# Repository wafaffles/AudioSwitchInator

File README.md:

# Audioswitchinator
A multi input and output audio switch with an integrated, toggleable Hifi phono preamp

## Shortcuts
- [Features](#features)
- [What is it?](#what-is-it)
- [Resources](#resources)
- [Assembly](#assembly)
- [Bill Of Materials](#bill-of-materials)
- [Photos](#photos)

## Audioswitchinator Zine

## Features
- 4 Inputs
  - 3 RCA
  - 1 3.5mm
- 2 Outputs
  - 2 RCA
- Audio Input and Output Selection
- Integrated Toggleable Phono Preamp for a Turntable

## What is it?

The Audioswitchinator is a device that was made to allow me to route all of my audio inputs and outputs into one place on my desk so that I can easily change where my audio is coming from and going to without having to deal with changing the input on my speakers, changing the output on my computer, and my record player mainly. It features 4 inputs, 3 RCA and 1 3.5mm ports, and 2 ouputs, both being RCA ports. The first of the phono inputs is routed to a toggleable phono preamp, based on this design by [Elliott Sound Products](https://sound-au.com/project06.htm). The mixture of inputs and ports allows for easily compatibility with most audio products, as well as supporting smaller on the go inputs like a phone or other input device. While I only need 2 inputs and 2 outputs currently, the device features the extra inputs and outputs as my equipment arsenal expands or I want to test new products without fully removing the old ones.

The device features a power switch on the rear to power the integrated phono preamp, a switch on the front to enable routing of the turntable input through the phono preamp, a rotary switch to choose which input you would like to listen to, and a switch to choose between either of the two inputs.
It is powered using 12V via a 5.7mm barrell jack. It has a very low power draw of around 50mA at most so nearly any suitable 12V switching mode power supply should work well.

The case is fully 3d printed with use of a few M4 bolts and heatset inserts, but can easily be modified to thread directly into the plastic. The design resembles the design pattern of Schiit Audio products as I currently own a DAC and headphone amp and really like the design. The case is at largest 160x80, so it is easily printable on most 3D printers, being designed to print on my Bambu Labs A1 Mini.

## Resources

CAD Link: https://cad.onshape.com/documents/9e04128c642e582e05c8193e/w/29af00c33977f5103195c9e0/e/9dcbf64564f57b3e7e8e01ad?renderMode=0&uiState=6a12269c000845437493f06b

CAD Files: [HERE](/Models)

ECAD Files: [HERE](/Models/ECAD/)

Production Files: [HERE](/Resources/)

## Assembly

You will need:
- PCB from files
- Soldering Iron & Solder
- All components from [BOM](https://docs.google.com/spreadsheets/d/1tNDlkv8S-ZhfvEyZw77WZDcWJRZpA8B7S98ZAzSkEbk/edit?usp=sharing.)
- Matching screwdriver to screw set (allen key in provided kit)
- Small pair of tweasers

To start, you will need to have access to a 3D printer with a build volume of at least 160x80mm and about 100-120g of filament of your choice.

You then need to order all the parts and PCB and have proper resources to solder these components. Once you have these, solder all components on as specified in the schematic.

Once soldered together where listed in the schematic, then with the bottom part of the case, insert the 8 heatset inserts if you choose not to modify the design to use those. To insert heatset inserts, get the largest tip that fits inside the heatset insert and install it on your soldering iron. Now, place the insert where it goes and insert the tip into the center of the insert snd heat it while applying slight downward force until it is flush with the surface. A small pair of tweasers may be helpful to reorient it.

Once all the heatset inserts are installed, you should be able to screw in the PCB, then screw on the top, and it should be working there!

## Bill Of Materials

Bill of Materials: [HERE](https://docs.google.com/spreadsheets/d/1tNDlkv8S-ZhfvEyZw77WZDcWJRZpA8B7S98ZAzSkEbk/edit?usp=sharing)

## Photos

Audioswitchinator PCB Schematic

Audioswitchinator Case Front

Audioswitchinator Case Back

Audioswitchinator Case Inside

PCB All Layers

PCB F.Cu Layer

PCB In1.Cu Layer

PCB In2.Cu Layer

PCB B.Cu Layer

Fromt of PCB

Back of PCB

## Credits

This project uses:

- [KiCad](https://www.kicad.org/)
- [Figma](https://www.figma.com/)
- [Hack Club Fallout](https://fallout.hackclub.com/path)

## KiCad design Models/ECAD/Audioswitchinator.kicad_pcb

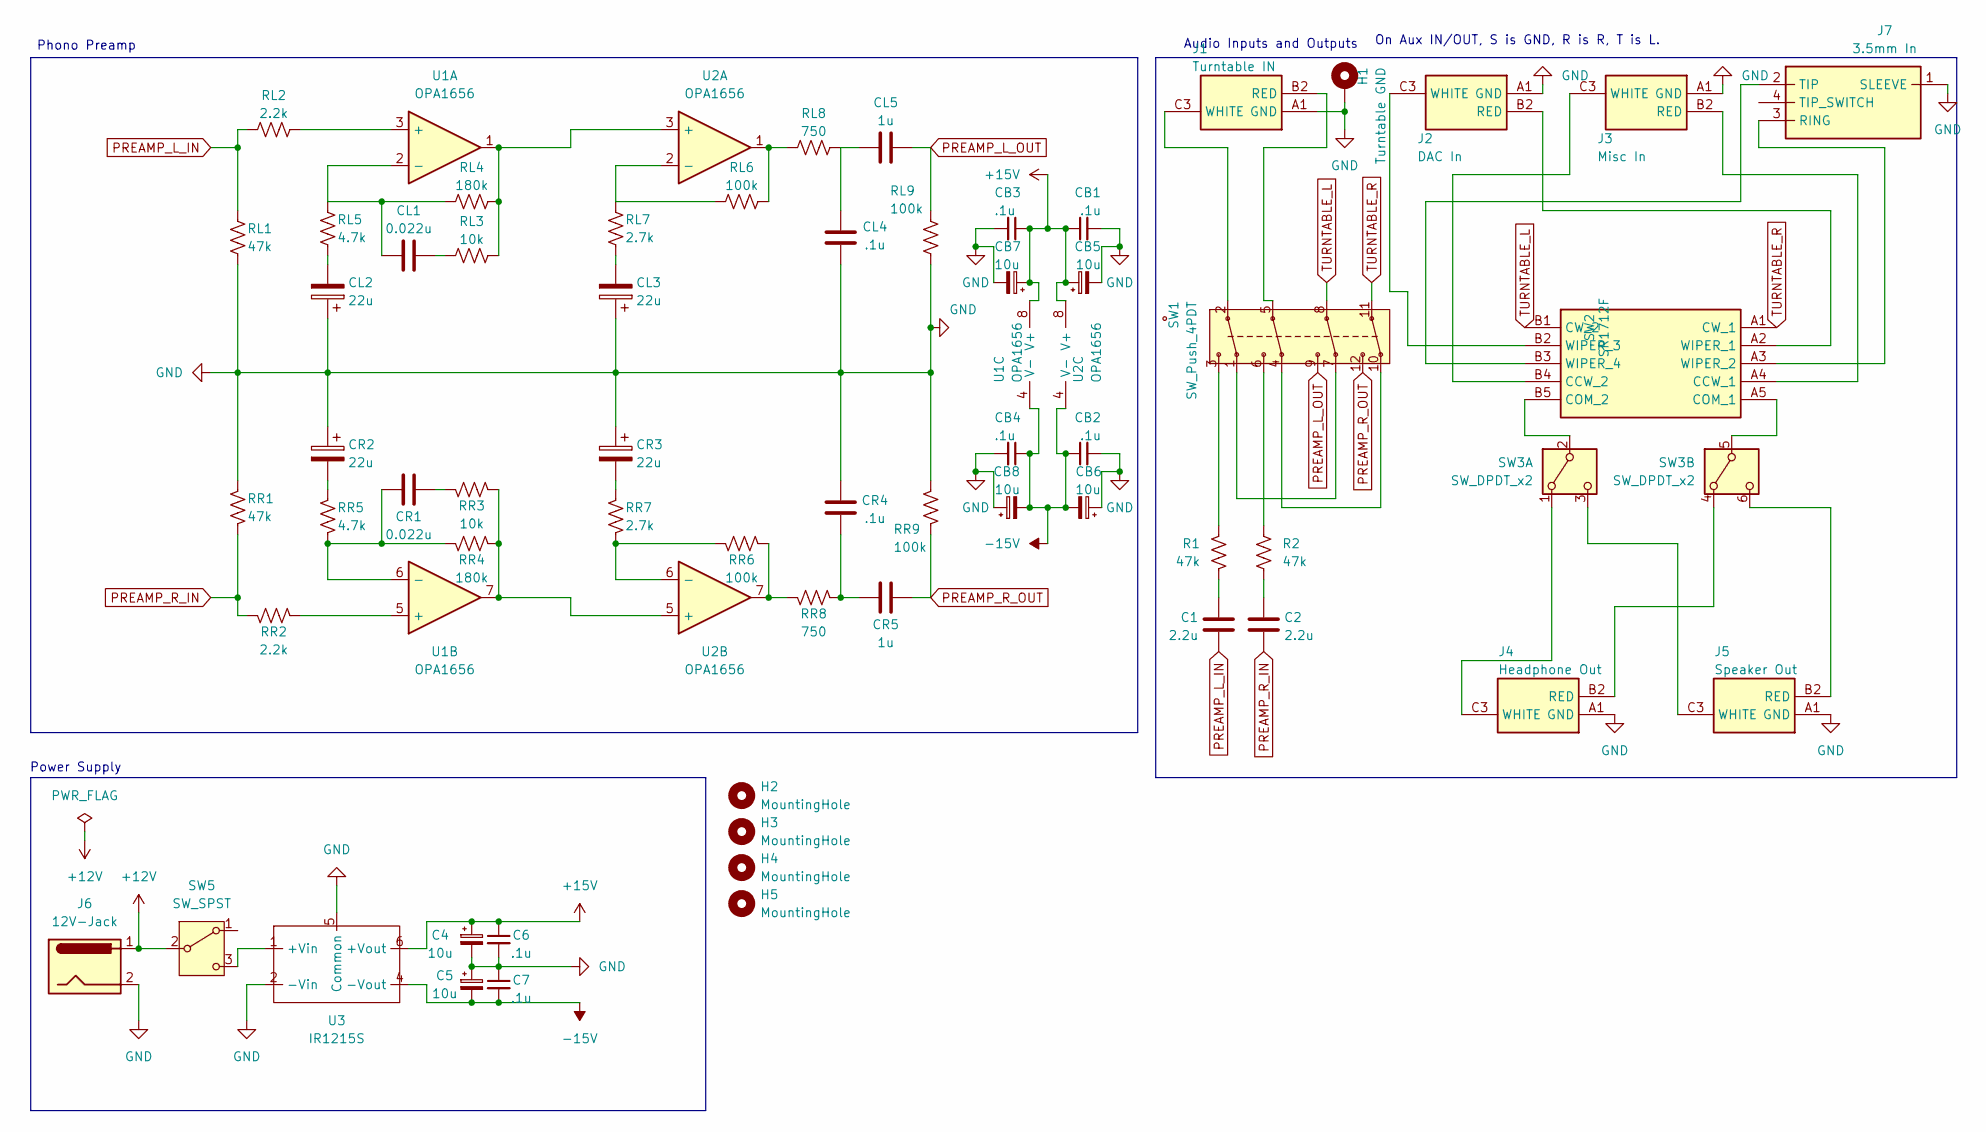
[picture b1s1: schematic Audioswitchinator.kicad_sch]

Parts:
C1, C2: 2.2u; C_Radial_D5.0mm_H11.0mm_P2.00mm
C4, C5: 10u; CP_Radial_D5.0mm_P2.00mm
C6, C7: .1u; C_Rect_L7.2mm_W2.5mm_P5.00mm
CB1, CB2, CB3, CB4: .1u; C_Rect_L7.2mm_W2.5mm_P5.00mm
CB5, CB6, CB7, CB8: 10u; CP_Radial_D5.0mm_P2.00mm
CL1: 0.022u; C_Rect_L13.0mm_W4.0mm_P10.00mm_FKS3_FKP3_MKS4
CL2, CL3: 22u; CP_Radial_D6.3mm_P2.50mm
CL4: .1u; C_Rect_L7.2mm_W2.5mm_P5.00mm
CL5: 1u; C_Radial_D5.0mm_H11.0mm_P2.00mm
CR1: 0.022u; C_Rect_L13.0mm_W4.0mm_P10.00mm_FKS3_FKP3_MKS4
CR2, CR3: 22u; CP_Radial_D6.3mm_P2.50mm
CR4: .1u; C_Rect_L7.2mm_W2.5mm_P5.00mm
CR5: 1u; C_Radial_D5.0mm_H11.0mm_P2.00mm
H1: Turntable GND; SolderWirePad_1x01_SMD_3x6mm
H2, H3, H4, H5: MountingHole; MountingHole_4.3mm_M4_Pad
J1: Turntable IN; 1564219E; Manufacturer_Part_Number 156-4219-E
J2: DAC In; 1564219E; Manufacturer_Part_Number 156-4219-E
J3: Misc In; 1564219E; Manufacturer_Part_Number 156-4219-E
J4: Headphone Out; 1564219E; Manufacturer_Part_Number 156-4219-E
J5: Speaker Out; 1564219E; Manufacturer_Part_Number 156-4219-E
J6: 12V-Jack; PJ059A
J7: 3.5mm In; SJ13554NG; Manufacturer_Part_Number SJ1-3554NG
R1, R2: 47k; R_1206_3216Metric_Pad1.30x1.75mm_HandSolder
RL1: 47k; R_1206_3216Metric_Pad1.30x1.75mm_HandSolder
RL2: 2.2k; R_1206_3216Metric_Pad1.30x1.75mm_HandSolder
RL3: 10k; R_1206_3216Metric_Pad1.30x1.75mm_HandSolder
RL4: 180k; R_1206_3216Metric_Pad1.30x1.75mm_HandSolder
RL5: 4.7k; R_1206_3216Metric_Pad1.30x1.75mm_HandSolder
RL6, RL9: 100k; R_1206_3216Metric_Pad1.30x1.75mm_HandSolder
RL7: 2.7k; R_1206_3216Metric_Pad1.30x1.75mm_HandSolder
RL8: 750; R_1206_3216Metric_Pad1.30x1.75mm_HandSolder
RR1: 47k; R_1206_3216Metric_Pad1.30x1.75mm_HandSolder
RR2: 2.2k; R_1206_3216Metric_Pad1.30x1.75mm_HandSolder
RR3: 10k; R_1206_3216Metric_Pad1.30x1.75mm_HandSolder
RR4: 180k; R_1206_3216Metric_Pad1.30x1.75mm_HandSolder
RR5: 4.7k; R_1206_3216Metric_Pad1.30x1.75mm_HandSolder
RR6, RR9: 100k; R_1206_3216Metric_Pad1.30x1.75mm_HandSolder
RR7: 2.7k; R_1206_3216Metric_Pad1.30x1.75mm_HandSolder
RR8: 750; R_1206_3216Metric_Pad1.30x1.75mm_HandSolder
SW1: SW_Push_4PDT; 1004P3T2B4M7QE
SW2: SR1712F; SRBM149501; Mouser Part Number 688-SRBM149501
SW3: SW_DPDT_x2; 100AWDP1T1B4M6QE
SW5: SW_SPST; ATE1D6M310Z
U1, U2: OPA1656; SOIC127P600X175-8N-OPA1656IDR
U3: IR1215S

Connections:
+12V: J6.1, SW5.2 (B)
+15V: C4.1, C6.1, CB1.1, CB3.1, CB5.1, CB7.1, U1.8 (V+), U2.8 (V+), U3.6 (+Vout)
-15V: C5.2, C7.2, CB2.1, CB4.1, CB6.2, CB8.2, U1.4 (V-), U2.4 (V-), U3.4 (-Vout)
GND: C4.2, C5.1, C6.2, C7.1, CB1.2, CB2.2, CB3.2, CB4.2, CB5.2, CB6.1, CB7.2, CB8.1, CL2.1, CL3.1, CL4.2, CR2.1, CR3.1, CR4.2, H1.1 (1_1), J1.A1 (GND), J2.A1 (GND), J3.A1 (GND), J4.A1 (GND), J5.A1 (GND), J6.2, J7.1 (SLEEVE), RL1.1, RL9.1, RR1.1, RR9.1, U3.2 (-Vin), U3.5 (Common)
unnamed: C1.1, R1.1
unnamed: C2.1, R2.1
unnamed: CL1.1, RL3.1
unnamed: CL2.2, RL5.1
unnamed: CL3.2, RL7.1
unnamed: CL4.1, CL5.2, RL8.2
unnamed: CR1.1, RR3.1
unnamed: CR2.2, RR5.1
unnamed: CR3.2, RR7.1
unnamed: CR4.1, CR5.2, RR8.2
unnamed: J1.B2 (RED), SW1.5
unnamed: J1.C3 (WHITE), SW1.2
unnamed: J2.B2 (RED), SW2.A2 (WIPER_1)
unnamed: J2.C3 (WHITE), SW2.B2 (WIPER_3)
unnamed: J3.B2 (RED), SW2.A4 (CCW_1)
unnamed: J3.C3 (WHITE), SW2.B4 (CCW_2)
unnamed: J4.B2 (RED), SW3.4 (A)
unnamed: J4.C3 (WHITE), SW3.1 (A)
unnamed: J5.B2 (RED), SW3.6 (C)
unnamed: J5.C3 (WHITE), SW3.3 (C)
unnamed: J7.3 (RING), SW2.A3 (WIPER_2)
unnamed: J7.2 (TIP), SW2.B3 (WIPER_4)
unnamed: R1.2, SW1.3
unnamed: R2.2, SW1.6
unnamed: RL6.2, RL8.1, U2.1
unnamed: RR6.2, RR8.1, U2.7
unnamed: SW1.1, SW1.7
unnamed: SW1.4, SW1.10
unnamed: SW2.A5 (COM_1), SW3.5 (B)
unnamed: SW2.B5 (COM_2), SW3.2 (B)
unnamed: SW5.3 (C), U3.1 (+Vin)
unnamed: RL2.2, U1.3 (+)
unnamed: CL1.2, RL4.1, RL5.2, U1.2 (-)
unnamed: RR2.2, U1.5 (+)
unnamed: CR1.2, RR4.1, RR5.2, U1.6 (-)
unnamed: RL3.2, RL4.2, U1.1, U2.3 (+)
unnamed: RL6.1, RL7.2, U2.2 (-)
unnamed: RR3.2, RR4.2, U1.7, U2.5 (+)
unnamed: RR6.1, RR7.2, U2.6 (-)
PREAMP_L_IN: C1.2, RL1.2, RL2.1
PREAMP_L_OUT: CL5.1, RL9.2, SW1.9
PREAMP_R_IN: C2.2, RR1.2, RR2.1
PREAMP_R_OUT: CR5.1, RR9.2, SW1.12
TURNTABLE_L: SW1.8, SW2.B1 (CW_2)
TURNTABLE_R: SW1.11, SW2.A1 (CW_1)

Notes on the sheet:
Power Supply
Audio Inputs and Outputs
On Aux IN/OUT, S is GND, R is R, T is L.
Phono Preamp

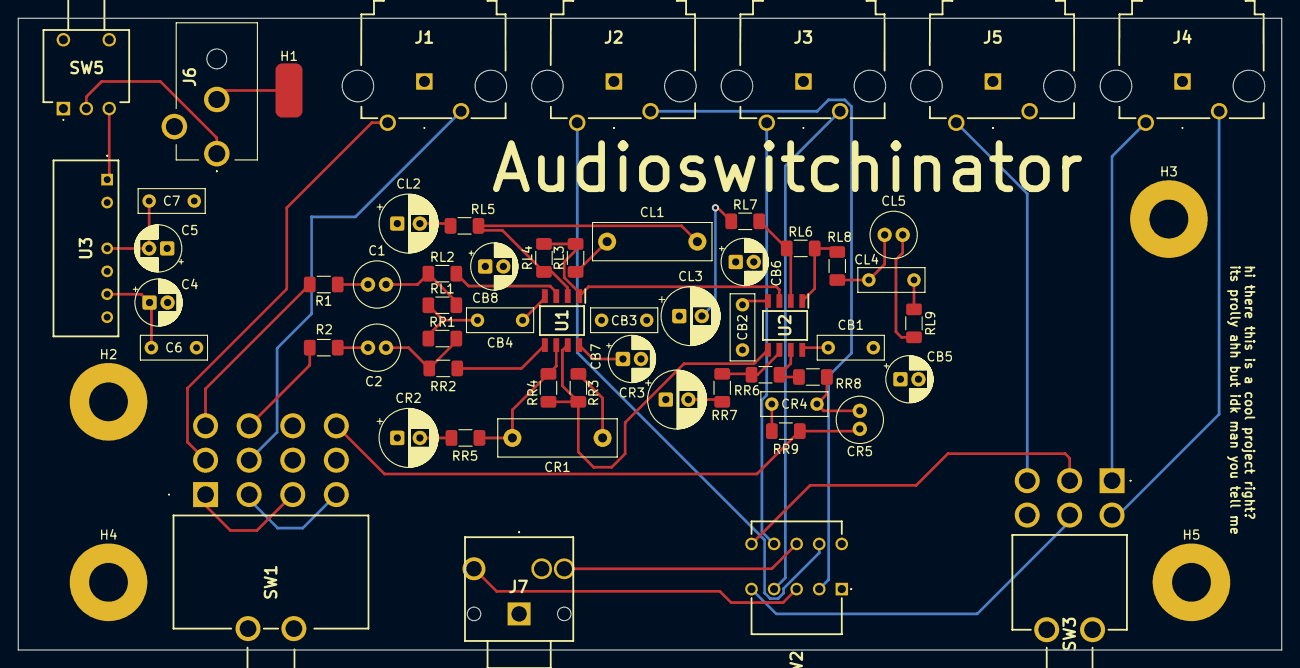
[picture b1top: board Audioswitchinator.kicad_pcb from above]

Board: 4 copper layers, 140.0 x 70.0 mm, 63 parts (0 on the bottom side), 49 nets.

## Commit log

2026-05-23 Update README.md
    Created first version of README, need to add BOM and files next
2026-05-25 Added Image, Fab, and Cad Files
2026-05-25 Create Test
2026-05-25 Added Images
2026-05-25 Create ECAD
2026-05-25 Create here
2026-05-25 upload ECAD files
2026-05-27 Sync local files with remote
2026-05-27 Force update all files
2026-05-27 Changes to folder paths
2026-05-27 Update Zine
